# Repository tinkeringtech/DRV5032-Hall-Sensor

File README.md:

# ScoutMakes DRV5032 Hall Effect Sensor Breakout

Detect magnets with ease using the ScoutMakes DRV5032 Hall Effect Sensor Breakout — a compact, beginner-friendly board built around Texas Instruments' ultra-low-power DRV5032 omnipolar Hall effect sensor.
Whether you're building a reed-switch replacement, detecting open/closed states on enclosures, or adding contactless triggering to your next project, this breakout gets you up and running in minutes.
Features

Ultra-low power — the DRV5032 is designed for battery-sensitive and always-on applications
Omnipolar detection — responds to both north and south magnetic poles
JST-PH 3-pin connector — plug-and-play wiring, no soldering required for compatible systems
CircuitPython ready — works out of the box with CircuitPython-compatible boards
OSHWA certified — open source hardware you can trust and build upon
Breadboard friendly — standard 0.1" header pitch for easy prototyping

Compatibility
Works great with Raspberry Pi, Arduino, and any microcontroller with a 3.3V or 5V digital input.
A Note on Sensor Variant
The DRV5032 comes in several variants that differ in switching threshold and output type. The current board ships with the DRV5032FBDBZR, but please be aware that the specific variant may change between production runs as component availability evolves. Always check the markings on the IC or the product page for the variant shipped with your order, and refer to the TI DRV5032 datasheet for full variant specifications before designing around a specific threshold.

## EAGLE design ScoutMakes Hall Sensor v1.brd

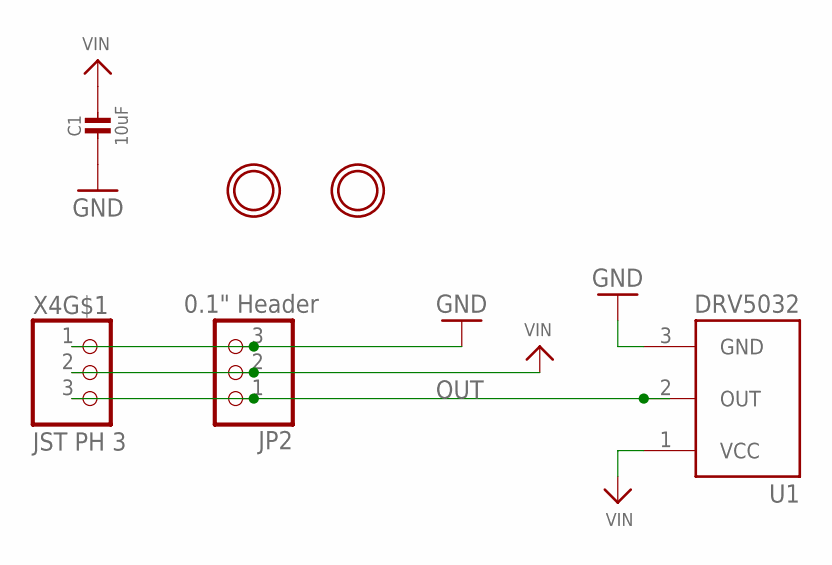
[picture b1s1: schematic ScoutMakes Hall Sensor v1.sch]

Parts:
C1: 10uF; 0805-NO
JP2: 0.1" Header; 1X03_ROUND
U1: DRV5055A1QDBZT; SOT95P237X112-3N
U$1, U$8: MOUNTINGHOLE2.5; MOUNTINGHOLE_2.5_PLATED
X4: JST PH 3; JSTPH3

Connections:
GND: C1.2, JP2.3, U1.3 (GND), X4.1
OUT: JP2.1, U1.2 (OUT), X4.3
VIN: C1.1, JP2.2, U1.1 (VCC), X4.2

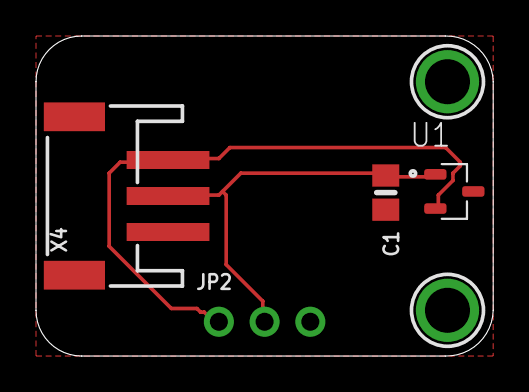
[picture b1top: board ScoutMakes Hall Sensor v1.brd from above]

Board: 2 copper layers, 25.4 x 17.8 mm, 6 parts (0 on the bottom side), 3 nets.

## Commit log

2024-08-18 Added schematics
2025-10-12 Added png of schematic for easy customer reference
2026-05-17 Revise README for ScoutMakes DRV5032 breakout
    Updated project description and features for clarity.

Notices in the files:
parts and their libraries:
microbuilder: This work is placed in the public domain, and may be freely used for commercial and non-commercial work with the following conditions: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
